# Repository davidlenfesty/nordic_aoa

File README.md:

# BLE Direction Finding

This is where I'm putting hardware and software for playing around with BLE direction finding with the nRF52811.

This is partly for getting direction finding support into NimBLE, but that depends on the timeframe and if I get the hardware done before any commercial hardware shows up.

## Hardware

There will be two boards, the tag, and the locator. Both will be dev boards, with a USB debugging interface (CMSIS-DAP or dap42 or something), some broken out pins, and the antennas.

To see an interactive bom, open $board/bom/ibom.html in a web browser.

### Tag

I will do this board first, to ensure that I can do the RF design, as I have never done any RF before.
It will just be a board with a USB debugging interface and a single antenna.

### Locator

This will be the "final product" and will have an array (3x3 or 4x4, haven't decided yet) of antennas to do the direction finding.

## Software

I'll have some firmware done at some point to actually do the playing around. It'll use Nordic's SDK to keep things simple.

## Progress

- [ ] Tag hardware design
    - [X] Schematic
    - [ ] BOM
    - [ ] Layout
    - [ ] Assembly / Verification
- [ ] Tag software bringup
    - [ ] Verify programming/non-BLE functionality
    - [ ] Verify it can act as BLE peripheral
    - [ ] Verify it has reasonable RF performance (doesn't need to be great, that's not the point here)
- [ ] Locator hardware design
    - [ ] Schematic
    - [ ] BOM
    - [ ] Layout
    - [ ] Assembly / Verification
- [ ] Locator software bringup
    - [ ] Verify peripheral/client functionality
    - [ ] Verify direction finding and antenna switching works
- [ ] NimBLE integration
    - [ ] Get boards to people who know what they're doing
    - [ ] ?????
    - [ ] Profit

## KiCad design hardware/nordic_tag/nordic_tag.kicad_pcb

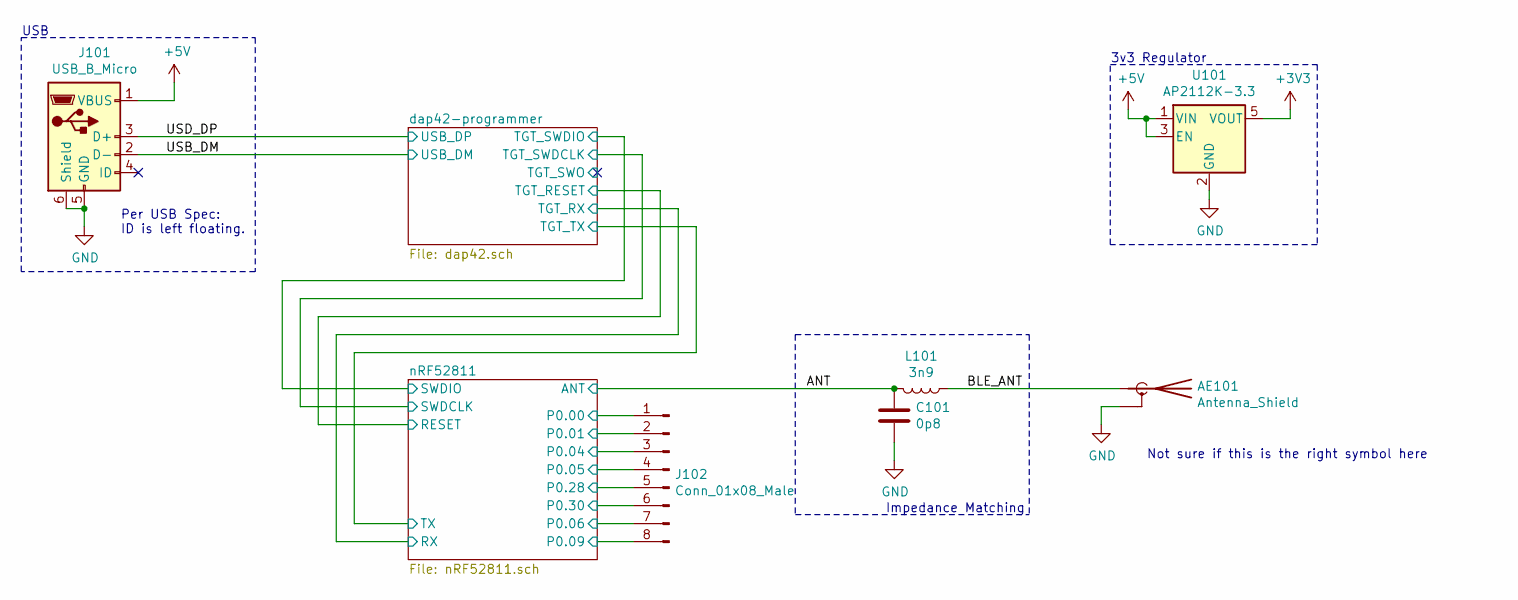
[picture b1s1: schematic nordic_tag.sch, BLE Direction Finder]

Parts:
AE101: Antenna_Shield; Texas_SWRA117D_2.4GHz_Right
C101: 0p8; C_0603_1608Metric
J101: USB_B_Micro; USB_Micro-B_Wuerth_629105150521
J102: Conn_01x08_Male; PinHeader_1x08_P2.54mm_Vertical
L101: 3n9; L_0603_1608Metric
U101: AP2112K-3.3; SOT-23-5

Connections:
+5V: J101.1 (VBUS), U101.1 (VIN), U101.3 (EN)
/ANT: C101.1, L101.2; also elsewhere on the board
/BLE_ANT: AE101.1 (A), L101.1
/USB_DM: J101.2 (D-); also elsewhere on the board
/USD_DP: J101.3 (D+); also elsewhere on the board
/nRF52811/P0.00: J102.1; also elsewhere on the board
/nRF52811/P0.01: J102.2; also elsewhere on the board
/nRF52811/P0.04: J102.3; also elsewhere on the board
/nRF52811/P0.05: J102.4; also elsewhere on the board
/nRF52811/P0.06: J102.7; also elsewhere on the board
/nRF52811/P0.28: J102.5; also elsewhere on the board
/nRF52811/P0.30: J102.6; also elsewhere on the board
GND: AE101.2 (Shield), C101.2, J101.5 (GND), J101.6 (Shield), U101.2 (GND); also elsewhere on the board

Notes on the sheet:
Impedance Matching
3v3 Regulator
Per USB Spec: ID is left floating.
USB
Not sure if this is the right symbol here

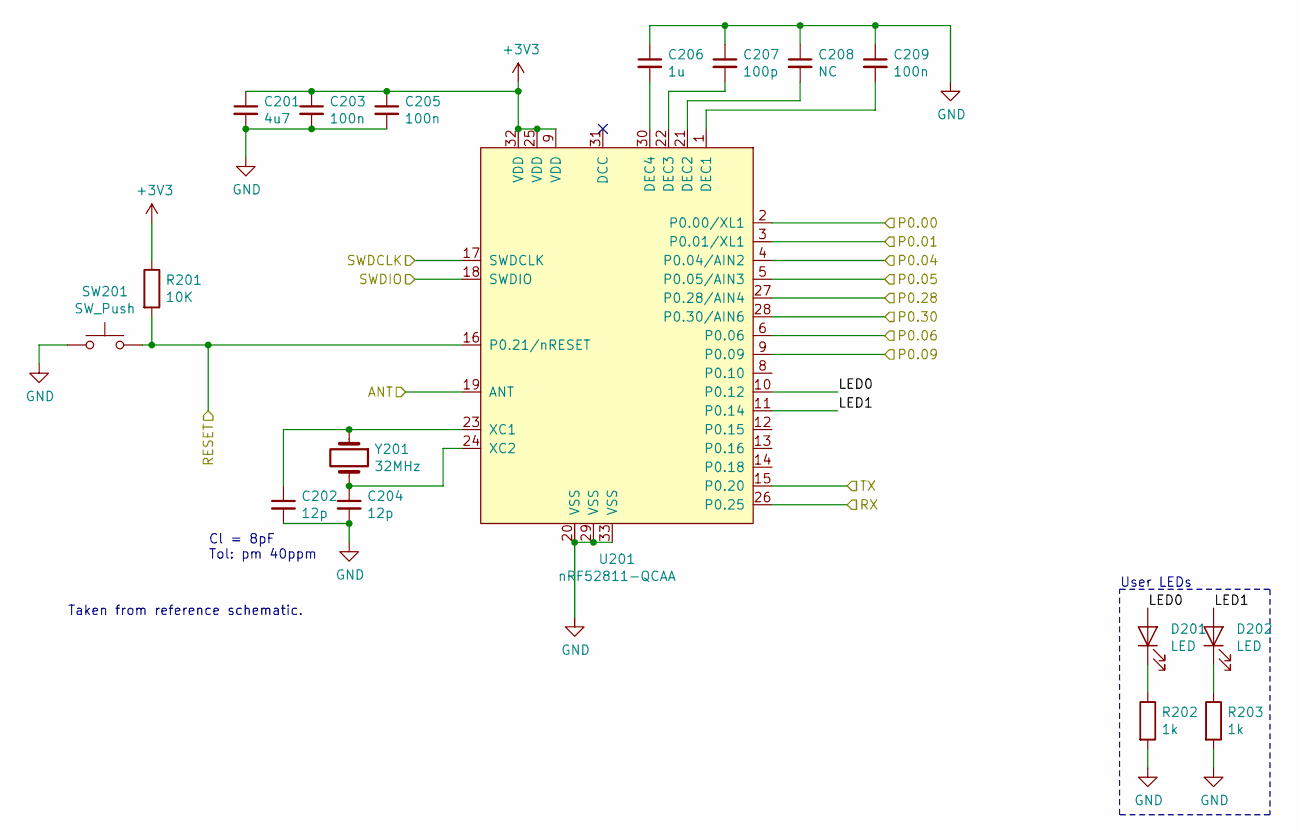
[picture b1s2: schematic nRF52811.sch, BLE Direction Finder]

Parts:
C201: 4u7; C_0603_1608Metric
C202, C204: 12p; C_0603_1608Metric
C203, C205, C209: 100n; C_0603_1608Metric
C206: 1u; C_0603_1608Metric
C207: 100p; C_0603_1608Metric
C208: NC; C_0603_1608Metric
D201, D202: LED; LED_0603_1608Metric
R201: 10K; R_0603_1608Metric
R202, R203: 1k; R_0603_1608Metric
SW201: SW_Push; SW_Push_1P1T_NO_CK_KMR2
U201: nRF52811-QCAA; QFN-32-1EP_5x5mm_P0.5mm_EP3.6x3.6mm
Y201: 32MHz; Crystal_SMD_5032-2Pin_5.0x3.2mm_HandSoldering

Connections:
/ANT: U201.19 (ANT); also elsewhere on the board
/dap42-programmer/TGT_TX: U201.15 (P0.20); also elsewhere on the board
/nRF52811/LED0: D201.2 (A), U201.10 (P0.12)
/nRF52811/LED1: D202.2 (A), U201.11 (P0.14)
/nRF52811/P0.00: U201.2 (P0.00/XL1); also elsewhere on the board
/nRF52811/P0.01: U201.3 (P0.01/XL1); also elsewhere on the board
/nRF52811/P0.04: U201.4 (P0.04/AIN2); also elsewhere on the board
/nRF52811/P0.05: U201.5 (P0.05/AIN3); also elsewhere on the board
/nRF52811/P0.06: U201.6 (P0.06); also elsewhere on the board
/nRF52811/P0.28: U201.27 (P0.28/AIN4); also elsewhere on the board
/nRF52811/P0.30: U201.28 (P0.30/AIN6); also elsewhere on the board
/nRF52811/RESET: R201.2, SW201.2, U201.16 (P0.21/nRESET); also elsewhere on the board
/nRF52811/RX: U201.26 (P0.25); also elsewhere on the board
/nRF52811/SWDCLK: U201.17 (SWDCLK); also elsewhere on the board
/nRF52811/SWDIO: U201.18 (SWDIO); also elsewhere on the board
GND: C201.2, C202.2, C203.2, C204.2, C205.2, C206.1, C207.1, C208.1, C209.1, R202.2, R203.2, SW201.1, U201.20 (VSS), U201.29 (VSS), U201.33 (VSS); also elsewhere on the board
unnamed: C202.1, U201.23 (XC1), Y201.1
unnamed: C204.1, U201.24 (XC2), Y201.2
unnamed: C206.2, U201.30 (DEC4)
unnamed: C207.2, U201.22 (DEC3)
unnamed: C208.2, U201.21 (DEC2)
unnamed: C209.2, U201.1 (DEC1)
unnamed: D201.1 (K), R202.1
unnamed: D202.1 (K), R203.1

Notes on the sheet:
Cl = 8pF Tol: pm 40ppm
Taken from reference schematic.
User LEDs

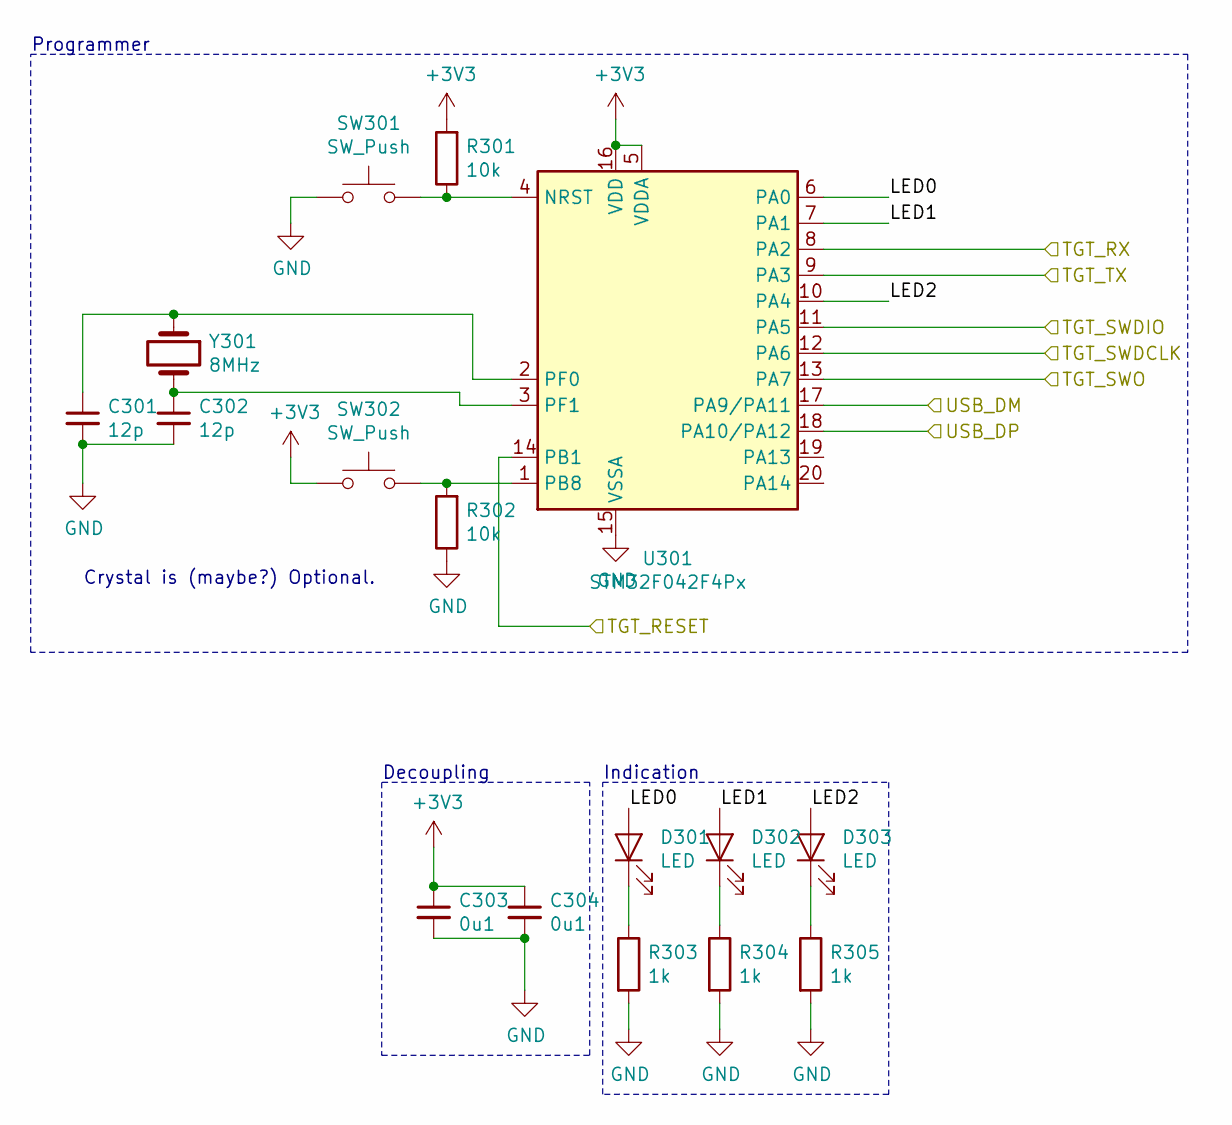
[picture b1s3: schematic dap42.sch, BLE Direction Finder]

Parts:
C301, C302: 12p; C_0603_1608Metric
C303, C304: 0u1; C_0603_1608Metric
D301, D302, D303: LED; LED_0603_1608Metric
R301, R302: 10k; R_0603_1608Metric
R303, R304, R305: 1k; R_0603_1608Metric
SW301, SW302: SW_Push; SW_Push_1P1T_NO_CK_KMR2
U301: STM32F042F4Px; TSSOP-20_4.4x6.5mm_P0.65mm
Y301: 8MHz; Crystal_SMD_5032-2Pin_5.0x3.2mm_HandSoldering

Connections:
/USB_DM: U301.17 (PA9/PA11); also elsewhere on the board
/USD_DP: U301.18 (PA10/PA12); also elsewhere on the board
/dap42-programmer/LED0: D301.2 (A), U301.6 (PA0)
/dap42-programmer/LED1: D302.2 (A), U301.7 (PA1)
/dap42-programmer/LED2: D303.2 (A), U301.10 (PA4)
/dap42-programmer/TGT_SWO: U301.13 (PA7)
/dap42-programmer/TGT_TX: U301.9 (PA3); also elsewhere on the board
/nRF52811/RESET: U301.14 (PB1); also elsewhere on the board
/nRF52811/RX: U301.8 (PA2); also elsewhere on the board
/nRF52811/SWDCLK: U301.12 (PA6); also elsewhere on the board
/nRF52811/SWDIO: U301.11 (PA5); also elsewhere on the board
GND: C301.2, C302.2, C303.2, C304.2, R302.1, R303.2, R304.2, R305.2, SW301.1, U301.15 (VSSA); also elsewhere on the board
unnamed: C301.1, U301.2 (PF0), Y301.1
unnamed: C302.1, U301.3 (PF1), Y301.2
unnamed: D301.1 (K), R303.1
unnamed: D302.1 (K), R304.1
unnamed: D303.1 (K), R305.1
unnamed: R301.1, SW301.2, U301.4 (NRST)
unnamed: R302.2, SW302.2, U301.1 (PB8)

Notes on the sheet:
Crystal is (maybe?) Optional.
Decoupling
Indication
Programmer

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
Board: 2 copper layers, 39 parts (0 on the bottom side), 40 nets, no tracks yet.

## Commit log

2019-11-05 Added README
2019-11-06 Added gitignore
2019-11-06 Mostly finished schematic
2019-11-06 Started PCB + BOM
2019-11-12 Switched to pcb antenna. started placement
